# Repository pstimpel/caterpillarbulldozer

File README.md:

# Caterpillar bulldozer
3D printed radio controlled bulldozer, 2 feet long

License: https://creativecommons.org/licenses/by-nc-sa/4.0/

Most obvious limits of this license:
- You are not allowed to use this stuff for commercial purposes
- You can download, reupload and change the stuff, but have to release it under the same license again
- You have the mention the origin, "Original by Peter Stimpel, https://github.com/pstimpel/caterpillarbulldozer/"

## Home of this project

https://github.com/pstimpel/caterpillarbulldozer/

### Other ressources

- Thingiverse: https://www.thingiverse.com/thing:4057714
- Prusaprinters.org: https://www.prusaprinters.org/prints/15078-caterpillar-bulldozer-rc
- Pinshape: https://pinshape.com/items/57510-3d-printed-caterpillar-bulldozer-rc

**Table of contents**
* [What's the story?](#what-s-the-story-)
* [A bulldozer!](#a-bulldozer-)
* [Sourcing parts, what do we need](#sourcing-parts--what-do-we-need)
+ [Filament, print instructions](#filament--print-instructions)
+ [Candy](#candy)
+ [Bearings](#bearings)
+ [Screws, nuts and bolts](#screws--nuts-and-bolts)
    - [M2](#m2)
    - [M3](#m3)
    - [M4](#m4)
+ [Electronics](#electronics)
    - [RC stuff](#rc-stuff)
    - [stuff for lights and buzzer](#stuff-for-lights-and-buzzer)
    * [Stuff to create a pcb](#stuff-to-create-a-pcb)
* [Let's build the bullozer now](#let-s-build-the-bullozer-now)
* [Who to thank?](#who-to-thank-)
* [Donation](#donation)
* [Feedback](#feedback)

## What's the story?

I run my hobby 3d printing for more than a year now. Yes, I am a noob. Along the way I looked for a software to do my CAD, and found Fusion 360 from Autodesk. So, I had to learn Fusion. Youtube offers great ressources, most important there is the Fusion 360 channel run by Autodesk (https://www.youtube.com/user/AutodeskFusion360). There is a bunch of lovely people with their tips and tricks - more details at the end of this. 

However, one day - I was finishing my illuminated death star (https://www.prusaprinters.org/prints/5661-death-star-illuminated-mood-lamp-death-star ), I was looking for a thing taking more than a few days to create. Something to be my project for the winter. And, I was keen to create something running on tracks. Now I dislike building replicas of war machinery, so a tank was no solution to me. 

## A bulldozer!

I was using my favorite search engine duck duck go, and found Caterpillar to be a big brand in the bulldozer manufacturers community. I sat down and thought what to do, and came up with these topics:

- no real replica, more a free style model of a bulldozer
- dimensions? who cares!
- radio controlled, and not steered by a gearbox, but two motors (I liked the challenge of learning how to program my radio control)
- the blade at the front should move up and down by servo motors

But how the f*** could I achieve these goals? I decided to create a gearbox first, add the motors to a motor stand, so I could test if running two independent tracks by an own motor each would be a cool thing. 

And what to tell: doing gears is easy enough in Fusion. I added some bearings, adjusted the tolerances, and had a working gearbox a few hours later. I mirrored it, added some dirty housing around, and created a design for the tracks.

Stearing two tracks having a motor each was not as easy as I thought. But the guys at (https://openrcforums.com) helped me out, so I got my radio control running quite soon. 

Next step: tracks. I designed a track in Fusion, printed the parts, screwed it together and started a very first test. This was the beginning of this story.

Video of the first test: 

Now, how to go on? Usually, you would design all the stuff, and once you are happy with your CAD, you print and assemble the stuff. I was going a different way. I designed the stuff during building the vehicle. Step by step both the CAD and the vehicle evolved. This caused some major mistakes and lot's of fun at the same time. I love it that way - CHAOS! One thing that was quite tough: you had to think about the next step, one step ahead, so you can connect the two steps somehow. Thank the lord there is candy ...

## Sourcing parts, what do we need

We need a 3d printer. I was using my Prusa I3 MK3. It has a build plate of 200x250, and Z is 200+. Some parts make use of these dimensions. If your printer has less build area, this project might not be for you, or you need to cut things apart. Of course we need tools. And, we need ...

### Filament, print instructions

I was using filament from my favorite supplier https://dasfilament.de. The print is PLA only, so I ordered about

- 6 spools yellow
- 1 spool transparent
- 2 spools black
- 1 spool anthracite
- 1 spool silver
- 1 spool white

Numbers are valid for printing in 0.3 layer height, using 3 shells horizontally and vertically, 10% cubic infill (except the gears and axles, I used 50% cubic infill here).

I was taking care not to need any support. I achieved this goal, except for very few parts.

The stls are not in their orientation for hassle free printing, I'm sorry. You do need to make this yourself in your slicer.

**Update upon user request**: If you find 3mf files to be more convinient to print, you might want to look at the folder "3mf-200x250". It contains 59 3mf-files. The orientation of the parts to print is set there already, also the numbers of parts to print is the right one already. To use these files your slicer has to support 3mf. Each of these files contains a full organized print bed, made for print beds equal to or larger than 200x250mm in dimension. Each filename is led by a number, which represents the order you should print the files. It contains as well an information for the filament color to use. "nocolor" means you can use a color of your choice since the files are hidden inside your bulldozer. 

### Candy

The build will take some time, not to talk about the 200 hours of printing. This means, it will be nerve-wracking :). Get some good stock of candy to please yourself once you enter mentally strange situations. I can tell you: you will need it!

### Bearings

We need 40 bearings of type 6700ZZ. Dimensions are 10x15x4mm. These are standard bearings, you should find them very easy. I ordered mine from https://www.kugellager-express.de/. 

We need another 12 bearings of type 6904 with dimensions 20x37x9mm. I ordered them from the same supplier.

### Screws, nuts and bolts

I order my stuff from a shop called https://www.schrauben-paul.com/. All given dimensions are mm. I did not count each single screw, so all numbers are estimates. However, if you enter such a project I expect you won't order exact counts.

#### M2
- 50 M2x8, cylinder head
- 50 M2x10, cylinder head
- 50 M2x16, cylinder head

#### M3
- 4 scrubscrews M3x6
- 4 square nuts M3
- 100 M3x10, cylinder head
- 100 M3x14, cylinder head
- 300 M3x20, cylinder head
- 100 M3x25, cylinder head
- 200 M3x45, cylinder head

#### M4
- 4 Bolts 40mm

### Electronics

I expect you have a radio control already. Therefore I do not link a receiver. But, you will need one 8 channel receiver matching your radio control and local laws. If you skip the lights part, a 4 channel receiver will do. As well, all my builds are ran by 2S Lipo, which means the voltage of the linked components below does match this battery type. If you go for a different voltage, please select your components in a way the match together.

#### RC stuff
- 2 standard servos, metal gear, metal servo arm (https://www.amazon.de/gp/product/B0716V3WNH/)
- 2 motors type 540, 55 turns or similar (https://hobbyking.com/de_de/1-10-540-carbon-brushed-motor-55t.html)
- 2 ESCs (https://hobbyking.com/de_de/hobbyking-x-car-45a-brushed-car-esc.html)
- 2 Lipo 2S, like (https://hobbyking.com/de_de/turnigy-nano-tech-shorty-4200mah-2s2p-65-130c-hardcase-lipo-pack-roar-approved.html)
- 2 connectors to connect your Lipos and ESCs

#### stuff for lights and buzzer
- Arduino Nano 5 Volt
- Resistor 0.25W 270 Ohm
- Buzzer 5 Volt (https://www.amazon.de/gp/product/B073RH8TQK/), we need the bigger one out of the package
- 1 switch like in (https://www.amazon.de/gp/product/B07MY2WVQ3)
- RGB leds (https://www.amazon.de/gp/product/B01N97A0XG)
- 3 cables for connecting receiver and Arduino, servo cables like (https://hobbyking.com/de_de/twisted-15cm-female-to-female-servo-lead-jr-22awg-10pcs-set.html)
- wires to connect the LEDs (https://www.amazon.de/gp/product/B01BI1G88C)
- 12 pin headers
- solder stuff, some shrinking tube 3mm

##### Stuff to create a pcb

We create a one sided, 60x60mm pcb. I expect you either have the stuff to do that because you know how to do it, or you just order the pcb from your favorite supplier. You can skip the pcb part completely, because it just controls the lights and the buzzer. If you do not need this, just order the rc stuff only. You could exchange your 8 channel receiver for a 4 channel receiver in this case as well.

But hey, no lights? Really?

**Warning**: I have still issues with flickering, randomly color changing LEDs, seems there is some noise coming from the ESCs and I need to filter those out. It is very likely the pcb design and parts list of the pcb will change soon.

## Let's build the bullozer now

**Remark**: if not mentioned any different, we talk about screwing things together using M3 screws. Just screw them into the plastic parts, make sure not going to fast when screwing them in. Friction causes heat, and heat cause melted plastic parts. Just be gentle. Do not overtighten the screws, there is no need for it. It is on you to determine the right length of a srew, just use common sense and do not try to mount a small handle using M3x45. 

We start with the gear box. Print all items in subfolder "BothSides" twice. Print items in "Housing", "LeftOnly" and "RightOnly" once each. The gears and axles need to be stable. I suggest you to print the axles horizontally aligned. Use some more dense infill on the gears and axles. 

Mount the motorstands to the base. Assemble all axle-gear combinations twice, once for left and one for right gearbox. Take note of the indexed axles, and their counterpart gears. Most gears have one side flat, while the other has kind of a builtin spacer. The spacer side points outside the axle, to the bearing. Axles A, B and C provide spacer parts, which sit in the middle between the gears.

Axle A is the one right after the motor. Axle B "connects" to Axle A and Axle C and so on. Should be straight forward. Do not miss the 6700 bearings, one at each end of each axle. Except "rearaxle", we will take care of those later.

Once all axles are assemnbled, use the "Gearboxbearingstands" to mount them at your gearbox base. Do this twice, for left and right gearset. Mount the outer housing "Gearhousing left/right". Make sure the gears can spin freely. Add the motors to the stands, fix them. The pinions are now mounted to your motors using 4 squarenuts and 4 scrubscrews M3. Add the supports and connector parts for Bearing holders and motorstands.

This is a good time to connect ESCs to the motors, Lipos to the ESCs and the receiver to the ESCs - for a very first test. **WARNING: Remove one of the positive voltage pins of your ESC before connecting them to your receiver**. This is **IMPORTANT**! If you miss this, **BLUE SMOKE** might appear out of your receiver and/or your ESCs. Bind the receiver to your radio control. I am using a mode 2 controller. My setup is like:

Channel 1 connected to left motor/esc, channel 2 connected to right motor/esc

* CH1 100 RUD * 100 ELE + 100 ELE
* CH2 -100 RUD * 100 ELE + 100 ELE

Check this out for more info (https://openrcforums.com/forum/viewtopic.php?f=5&t=12296), and kudos to the helpful gents over there.

And while we are at it, set CH 3 and CH6 both to P1, which will do the blade servo control.  

On top, set CH4 bound to ELE, and CH5 to RUD. CH4 and CH5 will connect to our Arduino for controling the LEDs and buzzer. If you dislike going for lights and buzzer, you can skip this last step completely. 

**Important**: Write down how you connected your ESCs to witch motor. If you push "forward", both axles have to turn forwards. If not, switch the connection between motor and ESC. Now push "forward" and "left". The left axle should go slower or stop completely, while the right axle turns forward. If it is the other way, just flip ESCs and restart this test. If you push backwards and left, the left axle should stop again, while the right axle turns backward. Check what happens if you "turn right". Do not go any further until you finished all this with a success!

Now print all parts from "LowerChassis". Print "InnerSupportLeft" and "InnerSupportRight" twice each. The numbers are ordered from front to back. Mount your assembled gearbox to the bottom using the support pieces. Use "InnerSupport..." to keep the bottom parts together. Add the rearaxles and their bearingholders. Do not forget to add the bearings of type 6904, 2 on each axle. Add the 6700 bearings to the outer end of both Axles "D", and the "Gear2AxleD-5edges" as well. Mount the "LowerChassis..." parts left and right. These keep all the other parts and axles in place. Add stability by making use of "InnerSupportLeft" and "InnerSupportRight".

It is printing time again: we print all the stuff from "Blade", "Drive" and "Tracksupport".

Print all parts once, except:

twice: BladeBarAxle, BladeHydraulicsBolt, BladeHydraulicsClamp, BladeHydraulicsTube. BladeServoBar, BladeServoLever, FrontAxle, FrontAxleDistancekeeper, UpperSupportAxle

four times: BladeServoLock, Wheel, UpperSupportSpacer, UpperSupportWheel

eight times: LowerSupportAxle

16 times: LowerSupportSpacer, LowerSupportWheel

52 times: ChainA, ChainB

Insert 6904 bearings into "BladeBarBearingHolder". Combine "BladeBarAxle" and "BladeBarLever", add 6904 bearings. Mount Axles using "BladeBarBearingHolder" Left/Right to the bottom. 

Add a 6904 bearing to the round end of the "FrontAxle". Add one "FrontaxleDistancekeeper" to the long side. Add a 6904 bearing to the longside. Mount it using the "FrontaxleBearingHolder". Do that twice for each side.

Now let's do the track supports. Mount two "LowerSupportWheel" at one "LowerSupportAxle", and put one "LowerSupportSpacer" on each end. Add a 6700 bearing at each end of the axle. Do this procedure eight times.

Mount two "UpperSupportWheel" at one "UpperSupportAxle", and put one "UpperSupportSpacer" on each end. Do this procedure twice.

Mount "TracksupportInnerLeft" to your chassis. Insert four of your "LowerSupportAxle" builds. Add "TracksupportOuterLeft" to your vehicle. Repeat this step at the right side using "TracksupportInnerRight" and "TracksupportOuterRight".

Starts to look serious, right?

Mount "TensionmountLeft" to your vehicle. Mount "TensionWheelholderInnerLeft", "TensionWheelholderOuterLeft", one of your "UpperSupportAxle" builds and "TensionBaseLeft". Mount this assembly to "TensionmountLeft" using a M3x45 screw.

Repeat this step for the right side of your vehicle.

Add the 4 wheels to your axles. Secure the wheels using M3#20 screws.

Time to build the tracks. We build two of them. So, 26 "ChainA" and 26 "ChainB" create one track, screwed together by 52 screws M3x45. The horn of "ChainA" points to the inside of our track loop, while the 3 edges of "ChainB" point to the outside. We screw the left track from the left side of the track, while we screw the right track from the right side. This will make it much easier to replace broken chain parts later on. Again, be careful with applying forces and heat out of friction. Depending on your screws they might have a non threaded part below the cylinder head. If so, use a 3.5mm drill to widen the holes of your chain parts, only the ones pointing away from your vehicle - the ones you start screwing in. Do not change the diameter of the holes the thread of your screw goes into. 

Great job, you have 2 tracks now. Mount the left one to the left side, the right one to the right side. Could be you need to lose your tension mechanisms again to make the tracks fit. There is a so called "TensionBlock" in the package "Tracksuppport". If your track is too lose, just mount one between "TensionBase" and the supportwheel assembly. Warning: do not tension your tracks like belts on your printer. They need to have some wiggle room. In case of doubts leave the "TensionBlock" away from your assembly.

If you like, this is the right time for a break. You could eat some candy, or drive around with your vehicle. Basic forward/backward and steering will work already. 

OK, let's move on. You will need to print the content of "UpperChassis" and "Grill". Mount all the "UpperChassisLeft/Right" parts using the support parts of that package. Parts 4 and 5 are connected directly to each other. Mount both servos to the servo mount. The servohead should point to the right side, backwards. Mount this assemblies to the upper chassis. Now mount the "BonnetSupport" parts on top of the upper chassis. Mount the CAT Logo and the Tailgate as well to the back.

Mount the round shaped servo head to the servos. Mount the "Bladeservolever" to the servohead. Once finished, the lever should point straight downwards, at both servos. Mount the BladeServoBar to it, and lock it using 2 of the BladeServoLocks.

Mount the upper chassis assemby to your vehicle. Use the left support parts out of the UpperChassis package to do that. 

Connect the BladeServoBar to its BladeBarLever, use the two remaining BladeServoLocks. I am sorry, but there is not much room to do that. You will make it. If not, remember your stock of candy, take a break, and try again. 

Time to assemble the grill. Print 4 sets of the LEDHousing package. Connect "GrillLeft", "GrillRight" and "GrillInsert". Add the CAT Logo to the "GrillInsert". 

If you go for the lights option: At this point you should have your pcb, equipped with the Arduino, pin headers, buzzer and resistor. Orientation of the board: you look at your Arduino, not the solder side of the PCB. USB of your Arduino is pointing to the left, the buzzer is top left. Connect CH4 of your receiver to the up right pin header. Connect CH5 to the pin header next left to the up right pin header. Cut the left servo cable in half. Use one half, solder the switch to the both outer pins, connect this to the lower left pin header of your PCB - the orientation of the connector does not matter. If you did it right, one pin header is left unconnected. Now, break 2 LEDs free of your LED "matrix", and do that 4 times. Take care of not confusing DIn and DOut direction. Connect the left servo cable half. Connect the black wire to ground on the DIn side of your leds. Connect the opposite wire to Voltage 5V. Connect the middle pin to Din. Now connect DOut of that LED with DIn of the next LED. Connect ground and 5V of both LEDs as well. Create 15cm long wires, my advice is to use 3 different colors. Connect these wires to the DOut, 5V and ground of LED 2. We go on with this scheme. Never ever confuse DIn, DOut, 5V and Ground. See the following scheme for wire lengths:

Servo plug -> 15 cm -> LED1 -> direct connection -> LED2 -> 15cm -> LED3 -> direct connection -> LED4 -> 65cm -> LED5 -> direct connection -> LED6 -> 40 cm -> LED7 -> direct connection -> LED8 -> 25 cm -> strobe lights assembly below.

Now we need to break free 4 sets of 3 LEDs in a row, each. 

Connect the 4 blocks of 3 LEDs each as you did above. Scheme:

25cm cable from your assembly above -> LED9 -> direct connection -> LED10  -> direct connection -> LED11 -> 5 cm  -> LED12 -> direct connection -> LED13  -> direct connection -> LED14 -> 5cm -> LED15 -> direct connection -> LED16  -> direct connection -> LED17 -> 5cm -> LED18 -> direct connection -> LED19  -> direct connection -> LED20

Remember the candy ...

The lower numbered LED stays at the bottom, the higher numbered LED at the top of each single led housing assembly. Use LEDCase, insert the first LED assembly, add LEDGlas to the front slot, and close this housing using 2 M2x6 screws. Insert the first LEDHouse in the right side of your Grill. Make sure the screws of your LEDHouse point upwards. Repeat this steps for the 2nd LEDHouse. Make sure the lower numbered LED stays at the bottom. Mount the LEDHouse into the left part of your grill. 

Connect the servo plug of the LED to the right bottom pin header of your pcb. Make sure the ground pin points to the right!

Mount the Grill to the Supports of your UpperChassis. 

Mount both ESCs to "ElectronicsESCBase", you can use double sided tape. Screw it in between the supports. Connect both ESCs to the motors, according to the scheme you created earlier when testing your gearbox. Connect the switches of the ESCs to "ElectronicsSwitchBase". Mount the buzzer switch as well. Screw the Switchbase into its place.

Mount both CAT logos to the "BonnetFront". Mount "Bonnetfront" to your Grill assembly. 

Mount "ElectronicsCablechannel" and "ElectronicsBatteryBlocker", and mount this assembly to the left side of the UpperChassis supports. Use zipties to manage your cable stuff. The LED wire assembly goes straight to the back of your vehicle with the long cable you added between LEDs 4 and 5 (LED houses 2 and 3).

Mount "BonnetBaseLeft", "BonnetBaseRight" and "BonnetBackbase" together. Mount it to your vehicle. 

Mount the "BonnetHandle" to "BonnetLeft" and "BonnetRight", using M2x8. Insert "BonnetLockBoltLeft" into "BonnetLockcaseLeft", and screw it to "BonnetLeft". Repeat this step for the "right" parts. Use M2x12 screws, and make sure the "Bolts" can move freely, towards the front of the vehicle. 

Mount the Bonnets to the "BonnetHinge", mount the Hinge to the "BonnetHingeSupport". 

Mount this assembly to the "BonnetFront" using 4 M3x14. 

Connect the "BonnetHingeSupport" and the "BonnetBackbase".

Mount "BonnetRear" at the end of the Bonnet stuff. 

Let's move on to the drivers cabine. Mount the "DriverCabBase" to the vehicle. Insert the LEDs 5/6 and 7/8 into the housings, again the lower numbered LEDs to the bottom, add the LED glasses and tops. Insert the LEDHouse 3 into the back left pocket of the "DriverCabBase", and LEDHouse 4 to the right pocket. Manage the cables. 

Mount "DriverCabBack", "DriverCabFront" and "DriverCabRoofSupport". Fiddle the left LEDs through the hole of the rear right Cabine Support. Mount "DriversCabLowerTop" to the vehicle. 

Mount "StrobeHousing" to "DriversCabUpperTop". Fiddle the left LEDs through the hole. Insert the LEDs into the housing, by putting the cables between these 4 LED strips in the center of the housing. Mount the top the vehicle. Mount the "StrobeGlas" to the "StrobeHousing" using M2x8. The "Glas" has indexed holes, keep this in mind. 

Now let's move on to the very last steps of our assembly, and therefore the finish line.

Before you mount the blade, you could of course take the opportunity to clear your candy stock, or you could drive around with your vehicle. To make sense of the light stuff, you would have to upload the arduino code to your Arduino first. However, it should beep if you drive forward/backward. On driving forward, the front light should be white, the backlight should be red. If you turn left or right the according LEDs should flash. The strobe should "turn" all the time. If you confused left or right during LED assembly, just change the numbers of the LED in your arduino sketch. Hint: You mighg have a hard time to plug the USB in and out of your Arduino. There are short Mini USB extension cables available. This cable will make your life easier.

Mount "BladeBarLeft" and "BladeBarRight" to the axles of your Blade servos. Fix them using some M3x20. Assemble the Blade now. "BladeLeft", "BladeMiddle" and "BladeRight" have holes for those M4 bolts. Insert them, and push the three Blade-parts together. Use screws to fix them at their backside. Add the "BladeEdge.." parts, using M2x8 screws. Mount "BladeHydraulicsHolderLeft" and "BladeHydraulicsHolderRight" to the blade. Mount "BladeHydraulicsGrillBaseLeft" and "BladeHydraulicsGrillBaseRight" to the "BonnetFront". Mount the "BladeHydraulicsTube" using "BladeHydraulicsClamp" to the "BladeHydraulicsGrillBase", make sure the tube is clamped around its half. Mount "BladeHydraulicsBolt" and "BladeHydraulicsBladeBase" together, twice. Mount these to the both "BladeHydraulicsHolder". Insert the "BladeHydraulicsBolt" into the Tubes.

**Whoooohoooo! Done!**

## Who to thank?

I want to thank the guys of DasFilament.de and Prusa Research (https://www.prusa3d.com/). You deliver stuff that works out of the box. No hassle, no tinkering. Love it.

Thanks a lot to Brad, Aaron, Angelo and all others from Autodesk Fusion 360 (https://www.youtube.com/user/AutodeskFusion360), who deliver a lot of knowledge in their videos. Without these "another little trick" stuff I would have not been able to finish this project. Still, my CAD project contains a lot of crime - but nothing you could not hide behind 3d printed parts.

Thanks to the 3d maker noob "3DMN" aka Joe (https://twitter.com/3dmakernoob) and the 3d printing nerd "3DPN" aka Joel (https://twitter.com/joeltelling/) for their video channels, and the know how they collect with their communities. Finally it was Joe from 3DMN who awakened my interest in Arduino stuff - check out his mood lamp. Please consider becoming Patrons if you like their stuff, as I do.

Thanks to the guys of 3dSets.com, they hooked me up to the world of 3d printing RC vehicles with their Rancher, which is a much easier to assemble RC car compared to this bullozer. Easier to build? Yep, because of a comprehensive manual they deliver.

Thanks as well to my colleague Jumbo, who answered some of my questions with his endless electronics knowledge.

Thanks to the guys from OpenRCForums (https://openrcforums.com). They just delivered the perfect solution to a RC noob like I am. I gained so much knowledge during this conversation - appreciated.

Thanks to my family! They have hard times seeing me cursing, or being away for hours to do soldering stuff. Finally, they have to share the home with a guy who loves melting plastics to turn it into vehicles, drones and other stuff.

## Donation

I spent hours over hours doing this. And I love doing it, it is my hobby. I really like to provide you this stuff for free. You should not feel bad by just downloading the stuff and using it according to the Creative Commons License (4.0, BY / NC / SA). 

However, if you would like to spend me a coffee, you can use Paypal https://www.paypal.com/paypalme2/RedZoneAction - thanks in advance.

## Feedback

If you go for a build, I would like it very much to hear from you. Maybe you want to share pics of your Bulldozer? You can find me at

https://twitter.com/PjotrS72

https://www.prusaprinters.org/social/2411-pstimpel/prints

https://www.thingiverse.com/pstimpel

## Finally...

I am providing this stuff as it is. I do not promise anything, and I am not responsible for any harm you might create or receive by following this manual or by using the methods and results described in this manual.

### Warning

Lipo batteries can cause danger. Handle them carefully. If you create PCBs on your own pay attention and take security measurements when handling chemicals.

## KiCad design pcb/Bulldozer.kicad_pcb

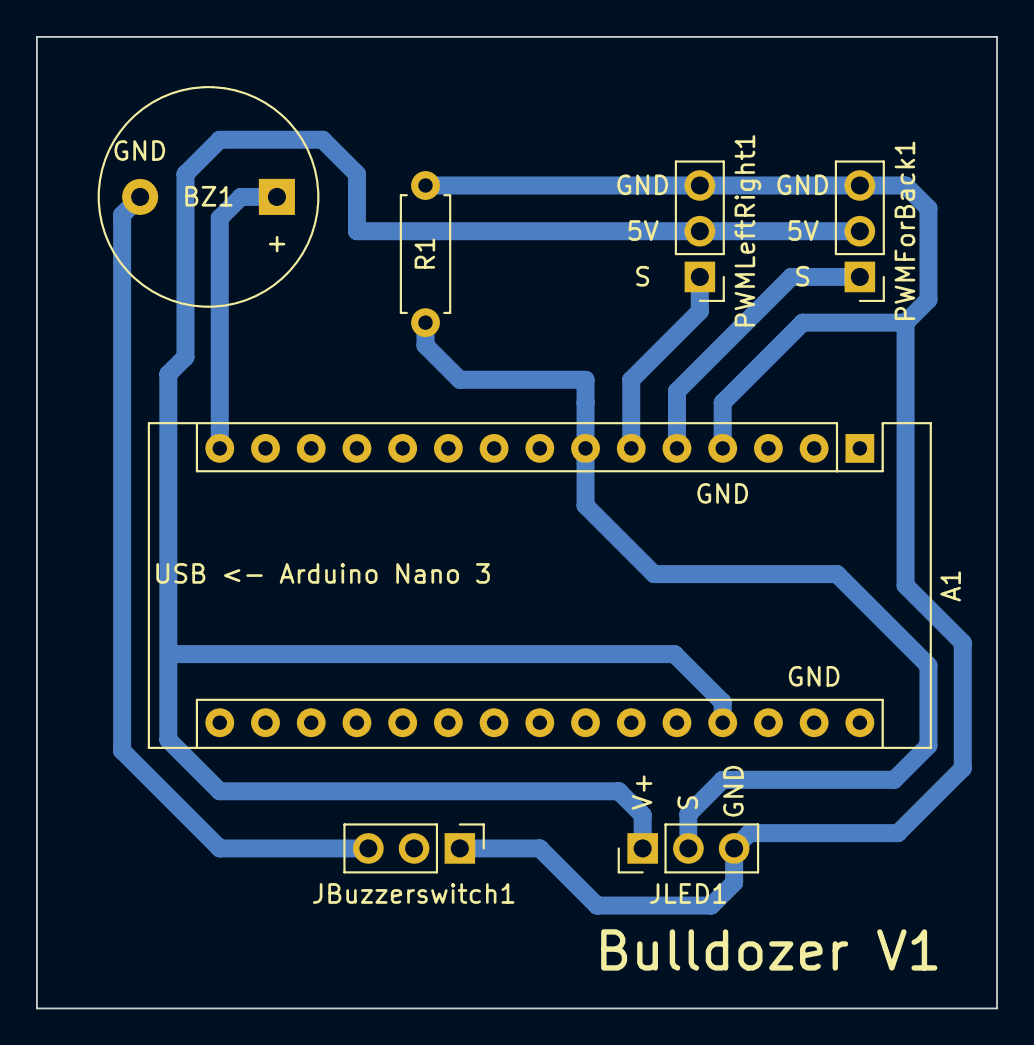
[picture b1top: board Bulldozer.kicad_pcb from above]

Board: 2 copper layers, 53.3 x 54.0 mm, 7 parts (0 on the bottom side), 7 nets.

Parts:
A1: Arduino_Nano_v3.x; Arduino_Nano
BZ1: Buzzer; Buzzer_12x9.5RM7.6
JBuzzerswitch1: Conn_01x03; PinHeader_1x03_P2.54mm_Vertical
JLED1: Conn_01x03; PinHeader_1x03_P2.54mm_Vertical
PWMForBack1: Conn_01x03; PinHeader_1x03_P2.54mm_Vertical
PWMLeftRight1: Conn_01x03; PinHeader_1x03_P2.54mm_Vertical
R1: 270; R_Axial_DIN0207_L6.3mm_D2.5mm_P7.62mm_Horizontal

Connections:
unnamed: A1.5, PWMForBack1.1
unnamed: A1.6, PWMLeftRight1.1
unnamed: A1.7, JLED1.2, R1.2
unnamed: A1.15, BZ1.1
unnamed: A1.27, JLED1.1, PWMForBack1.2, PWMLeftRight1.2
unnamed: A1.4, A1.29, JBuzzerswitch1.1, JLED1.3, PWMForBack1.3, PWMLeftRight1.3, R1.1
unnamed: BZ1.2, JBuzzerswitch1.3

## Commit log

2019-12-17 Readme, credential check
2019-12-17 Media
2019-12-17 Image test
2019-12-17 Readme
2019-12-17 Add license CC 4.0 by nc sa
2019-12-19 STLs added
2019-12-19 Picture added
2019-12-19 add more pictures
2019-12-19 Add Arduino sketch Add PCB layout file
2019-12-19 Next iteration of the manual
2019-12-20 Finalize Readme
2019-12-20 added cover pictures and more links
2019-12-20 Finalized
2019-12-22 Added 3mf files for more convenience Bugfix in README Bugifx in naming convention of stl file Gearbox/Housing/GearboxStandLeftUpper
2020-02-08 Update README.md
    Mistake removed to avoid user confusion
